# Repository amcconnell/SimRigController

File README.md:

# SimRigController

A Raspberry Pi appliance that turns Gran Turismo 7 telemetry from a PS5 into haptic feedback through bass shakers mounted to a sim-racing rig. The Pi listens for GT7's UDP telemetry on the LAN, derives audio effects (road bumps, engine rumble, brake/rev-limiter/wheel-slip buzz, gear-shift thumps) from packet contents in real time, and outputs to a shaker amp through a 3.5 mm jack (or DAC). A small web UI on the Pi lets you tune everything live from a browser or phone.

Originally built to replace a Windows tablet running SimHub just for shaker effects.

---

## How it works

```
PS5 (GT7)  ──UDP/33740──►  Pi 4 (shaker app)  ──audio──►  Fosi TP-02  ──speaker wire──►  bass shaker(s)
                                  ▲
                                  │ HTTP :80
                                  ▼
                            Browser / phone
                            (http://simrig-pi.local)
```

Inside the Pi, one Python process runs everything: an asyncio UDP client that decrypts (Salsa20) and parses GT7 packets, a FastAPI web app that hosts the tuning UI, and a PortAudio thread that mixes the configured effects.

Output is mono by default. Set `output_channels = 2` and the mix splits front/rear —
channel 0 (left) drives a front shaker, channel 1 (right) a rear one. Road vibration and
wheel slip are split by axle from real per-corner telemetry; the remaining effects are
placed with a per-effect bias slider. Setting it back to 1 reproduces the single-channel
output exactly, so it is a genuine escape hatch rather than a re-tune.

---

## Hardware

- **Raspberry Pi 4** (other Pi models work, but the deploy targets aarch64).
- **Bass shaker amp** — anything taking a line-level input and driving a shaker works.
  For front/rear you need *two amplifier channels*. Count the **speaker binding posts, not
  the input jacks**: mono subwoofer amps commonly have two RCA inputs that are summed
  internally to one channel, which merges front and rear back together.

  The rig here runs a **Fosi Audio V1.0G**: 2 channels, 50 W + 50 W, 2–8 Ω, 20 Hz–20 kHz
  ±1 dB, **input sensitivity ≤ 280 mV**, 19 V 4.74 A supply (12–24 V accepted),
  130 × 100 × 35 mm. Note the sensitivity — see [Audio output](#audio-output).
- **One or two bass shakers.** Two only helps if they are mounted somewhere your body can
  tell apart — a pedal deck and a seat work well, since that is feet versus back rather
  than asking you to localise a 50 Hz wave in space. On a bridged (BTL) stereo amp, wire
  **one shaker per channel**; two in parallel halves the impedance below what most boards
  tolerate.
- **A USB DAC** — see [Audio output](#audio-output). Worth having.
- **Ethernet or Wi-Fi** on the Pi, on the same LAN as the PS5.

---

## Audio output

The Pi's 3.5 mm jack is a **PWM-derived headphone output at roughly 0.4 V RMS**, where a
line output is about 2 V. A **class-compliant USB DAC** (~$10–30) gives you the latter, and
one with RCA outputs also removes the 3.5 mm splitter from the chain, which is worth doing
on its own.

On this rig the DAC was what finally produced usable output. Worth saying plainly, because
the datasheets do not predict that: the V1.0G is specified to reach rated output from
280 mV and the Pi's jack nominally clears that, so on paper the converter should have been
the only thing that changed. It was not. Treat published sensitivity figures as best-case
numbers and the Pi's PWM level as approximate — neither survives contact with a real rig,
and the amplifier's own volume control is the only calibration that counts.

Two things do come free with the swap. Getting off the PWM output improves low-level
linearity, which is where quiet road texture lives; and a DAC with **RCA outputs** deletes
the 3.5 mm splitter, a part that already cost an evening here when one conductor turned out
to be dead and presented as the software failing to separate channels.

Set the device by name substring in the UI (`aplay -l` to find it). Restart-required, so
the app bounces itself.

**USB adapters routinely enumerate attenuated.** The C-Media dongle used here comes up at
**-20 dB** — quieter than the Pi's own jack, and indistinguishable from "the DAC made no
difference", because nothing in the app can see it. The `simrig-alsa` unit installed by the
deploy sets output levels at boot, before the shaker service starts; see
`simrig_alsa_levels` in the `shaker_app` role. If a new adapter is quiet, check
`amixer -c <card> scontrols` first.

**Gain structure**, in order:

1. **Source at unity** — the DAC's own mixer at 100%, so the full converter range is used.
2. **Absolute level at the amplifier.** Set it once and mark the knob: everything tuned in
   software afterwards is relative to it.
3. **`master_gain` below the limiter.** If peaks sit at the ceiling the limiter clips the
   top off every transient, and the contrast between road texture and a kerb strike — the
   thing the effects exist to convey — goes flat. Around 0.5 suits a line-level source.
   **Diagnostics → Output limiter** measures this rather than leaving it to feel: it reports
   gain reduction in dB and the share of recent time spent reducing. Occasional reduction on
   the biggest hits is the limiter doing its job; reducing through most corners means the
   rig is being compressed, and the fix is less `master_gain` and more amplifier.
4. **`rear_gain_trim`** for the mechanical asymmetry between the two mounting points, then
   the per-effect bias sliders for placement.

Judge trim with **Test wiring**: both its pulses are identical in software and bypass
master gain, trim and the limiter, so any difference you feel is the rig rather than the
settings. Verify the trim you then set with **Test rev limit**, which is centred and goes
through the full chain.

**Run Test wiring before trusting any routing.** Nothing in software can detect reversed
speaker leads, and a swapped pair inverts every routing decision in a way that reads as
"feels subtly wrong" rather than as a fault.

---

## Pi setup (one-time)

Flash a fresh SD card with **Raspberry Pi Imager**:

1. Choose **Raspberry Pi OS Lite (64-bit, Bookworm)**.
2. Open advanced settings (gear icon) and set:
   - **Hostname**: `simrig-pi`
   - **Username**: `simrig`
   - **Password**: anything you'll remember (you'll need it for `sudo` during `ansible-deploy`).
   - **Wi-Fi** credentials (or use Ethernet).
   - **SSH**: enabled, with your Mac's public key authorized.
3. Boot the Pi, then from the Mac:

   ```sh
   ssh simrig@simrig-pi.local
   ```

   Confirm it logs in without a password prompt. Exit.

> If you use a different hostname or username, edit `ansible/inventory.yml` accordingly — `simrig-pi.local` and `simrig` are baked-in defaults the playbook assumes.

The Pi only needs SSH access and password-protected `sudo`. The deploy creates a separate unprivileged `shaker` user that the service runs as.

---

## Controller (Mac) setup

```sh
brew install ansible uv node
make ansible-deps        # one-time: pulls ansible.posix collection
make frontend-install    # one-time: installs npm deps for the UI
```

---

## Deploy

```sh
make ansible-deploy
```

This will:
- Install system packages (`libportaudio2`, `rsync`, etc.) on the Pi.
- Install [uv](https://docs.astral.sh/uv/) and pin it to a known version.
- Build the React UI on the Mac and rsync the bundle to the Pi.
- Create the `shaker` system user and `/opt/simrig/shaker/`.
- Run `uv sync --frozen` on the Pi to build a Python venv.
- Install and start the `shaker.service` systemd unit.

You'll be prompted once for the Pi's `sudo` password. The deploy is idempotent — re-running it is the normal way to ship code changes.

When it finishes, open **http://simrig-pi.local** on any LAN device.

### Useful targets

| Command                    | What it does                                                    |
| -------------------------- | --------------------------------------------------------------- |
| `make ansible-ping`        | Confirms SSH/Python connectivity to the Pi.                     |
| `make ansible-check`       | Dry-run with diff, no changes applied.                          |
| `make ansible-deploy`      | The real thing.                                                 |
| `make frontend-build`      | Build the UI bundle locally (chained by `ansible-deploy`).      |
| `make frontend-dev`        | Vite dev server, proxies `/api/*` to the live Pi.               |
| `make dev`                 | Run the Python service locally on the Mac (for backend hacking).|
| `make test` / `make lint`  | Python tests / ruff.                                            |

---

## Using the app

1. Make sure GT7 is **running on the PS5** and you're in an active session.
2. Open **http://simrig-pi.local** — the status pill should switch from `discovering` to `connected` within a few seconds.
3. The default profile is read-only — click **+ New** to create a tunable profile.
4. Drag sliders to taste; changes save automatically (~300 ms debounce).
5. The test buttons at the top of each effect fire a synthetic input so you can verify the audio path without driving — useful for setting a baseline gain.
6. On two channels, run **Test wiring** first — it pulses the front shaker, pauses, then the
   rear, bypassing every effect. Nothing in software can detect reversed speaker leads, and a
   swapped pair inverts every routing decision in a way that reads as "feels subtly wrong"
   rather than as a fault.

**Profiles** are named snapshots of the *tuning*. The built-in `default` profile lives in
code and can't be edited or deleted. Use them to keep separate tunings per car or per driver;
switching activates one instantly.

Profiles deliberately do **not** carry the **Rig** screen — audio device, sample rate, buffer,
output channels and rear trim. Those describe the machine rather than how you want it to feel,
and they do not stop being true because you switched from a GT3 setup to a road car. Keeping
the line there is what stops activating a profile from resetting a stereo rig to mono, and
what would let a profile mean the same thing on somebody else's hardware.

**Mute** toggles output without changing any config — useful for phone calls. It's in-memory
only and resets if the service restarts.

---

## Measuring instead of guessing

Tuning by feel has a specific failure mode: you are always comparing against a memory of a
different track, in a different car, days ago. Two tools exist to replace that.

**Diagnostics → Output limiter** reports gain reduction in dB and the share of recent time
spent reducing. Occasional reduction on the biggest hits is the limiter doing its job;
reducing through most corners means the mix is being compressed rather than driven, and the
symptom is not distortion but sameness — kerbs, shifts and road texture all arriving at one
level. That reads as "flat", whose obvious remedy is more gain, which makes it worse.

**Diagnostics → Session recording** captures every packet at full rate to
`recordings/session-*.jsonl`. Whole packets, including the menu and paused frames the app
itself discards, so a replay exercises the same gates the live path does. It stops itself at
256 MB.

`scripts/replay.py` then renders a recording back through the real DSP offline — no audio
device involved — so the same lap can be measured under two settings:

```sh
python scripts/replay.py recordings/session-20260807-1830.jsonl
python scripts/replay.py <file> --set master_gain=1.0
python scripts/replay.py <file> --profile "Gr.3" --against "road car"
python scripts/replay.py <file> --wav /tmp/lap.wav
```

Packets are scheduled by `packet_id`, GT7's physics frame counter, so replay is immune to
network jitter and two runs of one file are bit-identical.

Watch **crest** — peak over RMS — rather than peak. The limiter pins peak to the ceiling by
construction, so two settings that feel completely different report the same peak. Crest is
what collapses when a mix is being compressed:

```
delta (B - A)
   ch0: rms  +1.76 dB   crest  -1.65 dB
limiter: duty +52.0 pts   peak +18.06 dB

B is louder but flatter — dynamic range traded for level.
```

### Front/rear isolation

Two accelerometer pods (ADXL345 on I2C, `0x53` front and `0x1D` rear) measure what the rig
actually delivers. **Diagnostics → Accelerometer pods** shows live orientation and vibration;
**Measure crosstalk** pulses each shaker alone and reports how much reaches the other pod.

Read the **isolation** figure, which is the mean of the two directions. Per-pod sensitivity
error enters the two directions as reciprocals and cancels in the mean, so that number is
right even with the pods uncalibrated or badly matched — only the asymmetry between
directions carries the mismatch.

This matters more than it sounds. Below about 100 Hz a body does not localise a source; it
reports which part of itself is loaded, feet or back. So energy from the pedal deck arriving
at the seat is *felt as rear*, which is the exact cue the two-channel split exists to carry.

The rig here measures **-4.2 dB** — a seat plate bolted to a 1" hot-rolled steel frame, which
is close to an ideal transmission path at these frequencies. Isolating the plate would want
about 5 mm of static deflection under seated load to put the isolator's natural frequency near
7 Hz, and that compliance is felt every time you brace against the brake pedal.

The cheaper answer is to stop relying on position. Road vibration carries **separate noise
bands per channel** — rear low, front high — so the two ends differ in character rather than
location, which is the distinction a body still makes when the frame has mixed them together.

Be clear that this is a fiction: no road puts a particular frequency under one axle. It buys
discriminability at the cost of realism, and it is off by default (both channels ship with the
same 44-50 Hz and 60-80 Hz bands). The discrete effects have always been coded this way —
brake at 30 Hz, gear shift at 44, rev limiter at 75, slip at 90/65 — so the vocabulary already
exists; extending it to the continuous bed is the part worth deciding deliberately.

---

## Configuration

The Pi stores two config files in `/opt/simrig/shaker/config/`:

- **`shaker.toml`** — the live config (`[gt7]`, `[web]`, `[audio]` sections). The audio section is overwritten when you activate a profile. Edits via the web UI write here.
- **`profiles.json`** — your named profiles and the currently-active one. Created on first deploy, never overwritten on re-deploy.

You can SSH in and edit `shaker.toml` directly; the service watches the file and reloads on save. Restart-required changes (web host/port, audio device/sample-rate/buffer) trigger a clean systemd restart.

---

## Repo layout

```
SimRigController/
├── ansible/                 # Idempotent deployment to the Pi
│   ├── inventory.yml
│   ├── site.yml
│   └── roles/{base,python_runtime,shaker_app}/
├── apps/shaker/             # The Python app
│   ├── src/shaker/
│   │   ├── audio/           # Effect generators + mixer
│   │   ├── gt7/             # Salsa20 decrypt + packet parser + UDP client
│   │   ├── web/             # FastAPI + built React bundle
│   │   ├── config.py        # AudioConfig / Config dataclasses
│   │   ├── profiles.py      # Profile CRUD
│   │   └── runtime.py       # asyncio orchestrator
│   ├── tests/
│   ├── frontend/            # Vite + React + TS + Tailwind UI source
│   └── config/shaker.toml   # Default values shipped with the repo
└── Makefile
```

---

## Credits

The GT7 telemetry protocol (UDP port, Salsa20 key, packet layout) is community reverse-engineering; the Python port here is based on prior work from [gt_telem](https://github.com/snipem/gt-telem) and PDTools.

---

## License

MIT — see [LICENSE](LICENSE).

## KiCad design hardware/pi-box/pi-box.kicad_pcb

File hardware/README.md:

# Hardware

Printable parts for the rig.

## Which files to edit

**`ADXL_Pod_PD.FCStd` is the model.** It is a PartDesign document: open it in
FreeCAD, edit the `Params` spreadsheet, and every sketch follows. Sketches are
constrained and bound to spreadsheet aliases by expression, and each attaches
to an origin plane rather than to a face of an earlier feature — face
references are what make PartDesign models break when something upstream
changes size.

`build_adxl_pod_pd.py` built it once and is kept only to show the layout. It is
not re-run; the `.FCStd` is the source now.

`adxl_pod.py` is the earlier Part-primitive implementation. Kept as a
reference for the geometry rationale and because its assertions document the
two collisions found during design. **Read-only** — edits go in the PartDesign
model. Regenerate its own output, if ever needed, with
`freecadcmd hardware/adxl_pod.py`.

Both produce the same part: pod 34.31 cm^3 in each, lid within 0.01 cm^3.

After editing the model, re-export `ADXL_Pod_PD.stl` and `ADXL_Pod_PD_Lid.stl`
for slicing.

## ADXL345 sensor pod

Bolt-on enclosure for a GY-291 ADXL345 breakout, with an RJ45 keystone jack for
a Cat5 drop back to the Pi. One pod per contact point — seat pan and pedal deck.

Part of the accelerometer feedback loop: the shaker app has no input, so every
level it reports is the buffer it computed, upstream of the DAC, amp and
transducer. It reads identically whether a shaker is working or its cable is
cut. An accelerometer on the frame is what turns "does this feel balanced?"
into a number.

| | |
| --- | --- |
| Outer | 66 x 40 x 36 mm, ~43 g pod + ~12 g lid in PLA |
| Rig bolt | M5, counterbored so the head finishes below the board |
| Board | GY-291, 15.0 mm hole spacing, M2.5 heat-set inserts |
| Jack | AMPCOM HKJ-801M keystone, 14.7 x 19.6 aperture, 2 mm local wall |
| Lid | Snap-fit, 0.4 mm bead with a 0.45 mm lead-in ramp, pry notch |

### Assembly

1. Heat-set two M2.5 inserts into the pedestal.
2. Punch the keystone down onto short **solid-core** pigtails — IDC terminals
   bite solid wire, and stranded works loose under vibration. Snap the jack in
   from outside.
3. Bolt the pod to the frame **before** fitting the board; it covers the
   counterbore.
4. Screw the ADXL345 down, wire it to the pigtails, snap the lid on.

Second pod ties SDO high for I2C address `0x1D`; both share one bus.

### Things that are load-bearing, not stylistic

- **The pedestal.** Mount stiffness *is* the measurement. A compliant path adds
  its own resonance, and if that lands under ~120 Hz it reads as rig behaviour.
  The walls are a shell and carry nothing.
- **The counterbore.** It exists so the board can straddle the bolt rather than
  stand off above its head — which would rebuild the compliance the pedestal is
  there to avoid.
- **The 2 mm wall at the aperture.** Keystone latches are made for wall-plate
  stock and will not grip 3 mm.
- **The tight snap groove.** A rattling lid is a noise source on a part built to
  measure vibration. If it still rattles once printed, damp it with tape.
- **The bead's lead-in ramp.** Insertion and removal should not be the same
  fight: the ramp deflects the lip gradually on the way in, while the square
  top shoulder still does the retaining. If the lid ends up too loose, raise
  `BEAD` rather than removing the ramp — that restores grip without making it
  hard to fit again.

### Before printing 55 g

The keystone snap and the lid snap both come from drawings rather than calipers,
and both sit within FDM tolerance of not fitting. Slice the first 5 mm in X (the
keystone wall) and a short length of lid rim, and check the fits first.

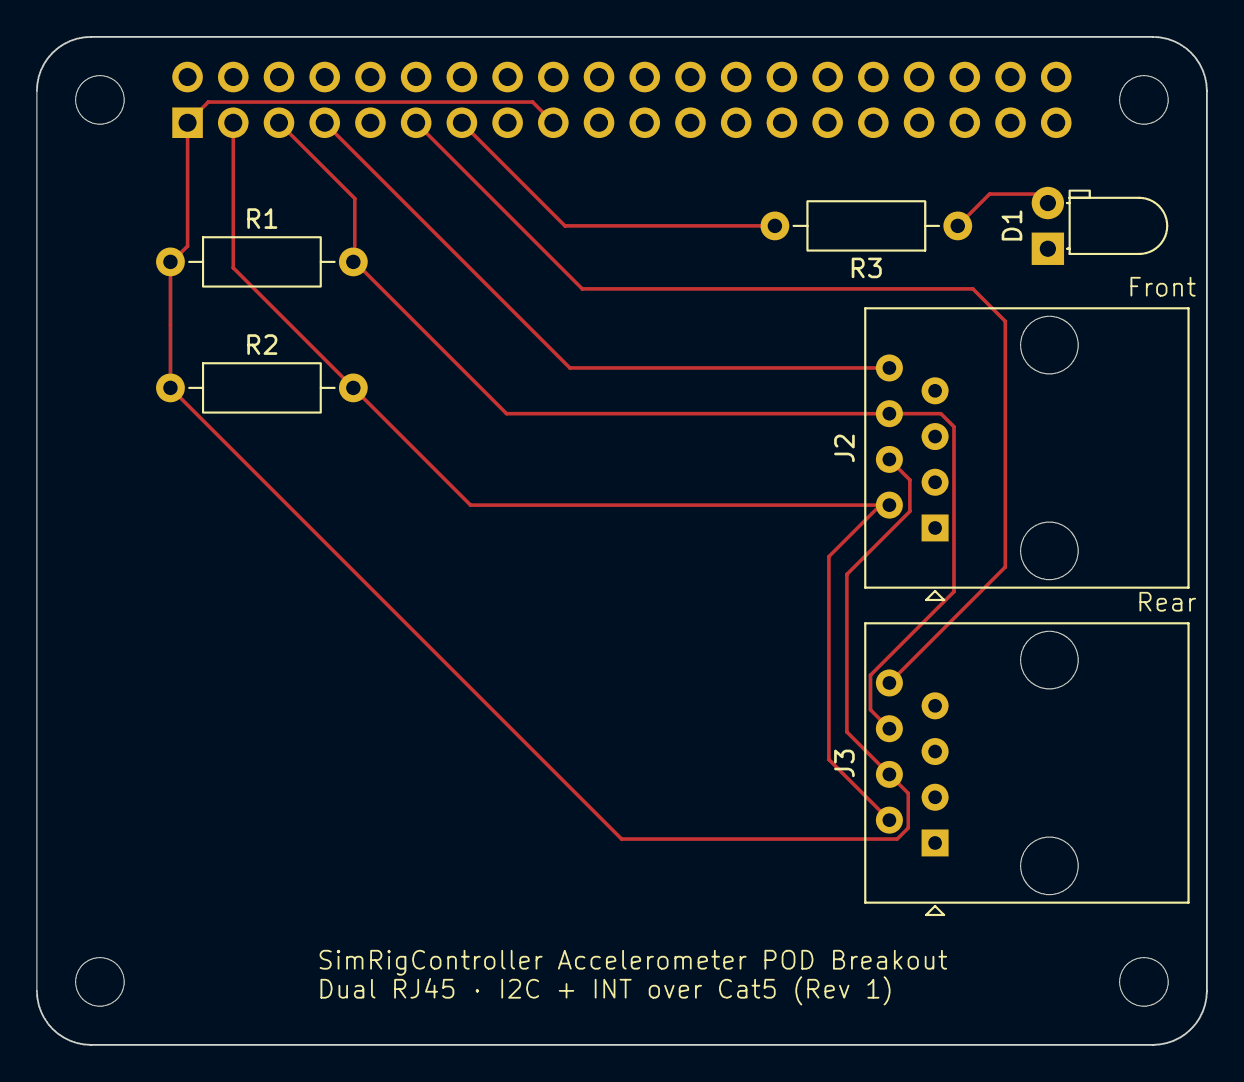
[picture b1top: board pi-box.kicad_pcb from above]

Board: 2 copper layers, 65.0 x 56.0 mm, 11 parts (1 on the bottom side), 8 nets.

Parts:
D1: LED; LED_D3.0mm_Horizontal_O1.27mm_Z10.0mm
J1: Raspberry_Pi_4; PinSocket_2x20_P2.54mm_Vertical
J2, J3: RJ45; RJ45_Amphenol_54602-x08_Horizontal
MH1, MH2, MH3, MH4: MountingHole_2.7mm_M2.5
R1, R2: 3.3k; R_Axial_DIN0207_L6.3mm_D2.5mm_P10.16mm_Horizontal
R3: 1k; R_Axial_DIN0207_L6.3mm_D2.5mm_P10.16mm_Horizontal

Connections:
+3.3V: J1.1 (3V3), J1.17 (3V3), J2.4, J3.4, R1.1, R2.1
/INT_FRONT: J1.7 (GPCLK0/GPIO04), J2.8
/INT_REAR: J1.11 (GPIO17/SPI1_~CE1), J3.8
/SCL: J1.5 (SCL_I2C1/GPIO03), J2.6, J3.6, R1.2
/SDA: J1.3 (SDA_I2C1/GPIO02), J2.2, J3.2, R2.2
GND: D1.1 (K), J1.6 (GND), J1.9 (GND), J1.14 (GND), J1.20 (GND), J1.25 (GND), J1.30 (GND), J1.34 (GND), J1.39 (GND), J2.1, J2.3, J2.5, J2.7, J3.1, J3.3, J3.5, J3.7
unnamed: D1.2 (A), R3.1
unnamed: J1.13 (GPIO27/SDIO_DAT3), R3.2
